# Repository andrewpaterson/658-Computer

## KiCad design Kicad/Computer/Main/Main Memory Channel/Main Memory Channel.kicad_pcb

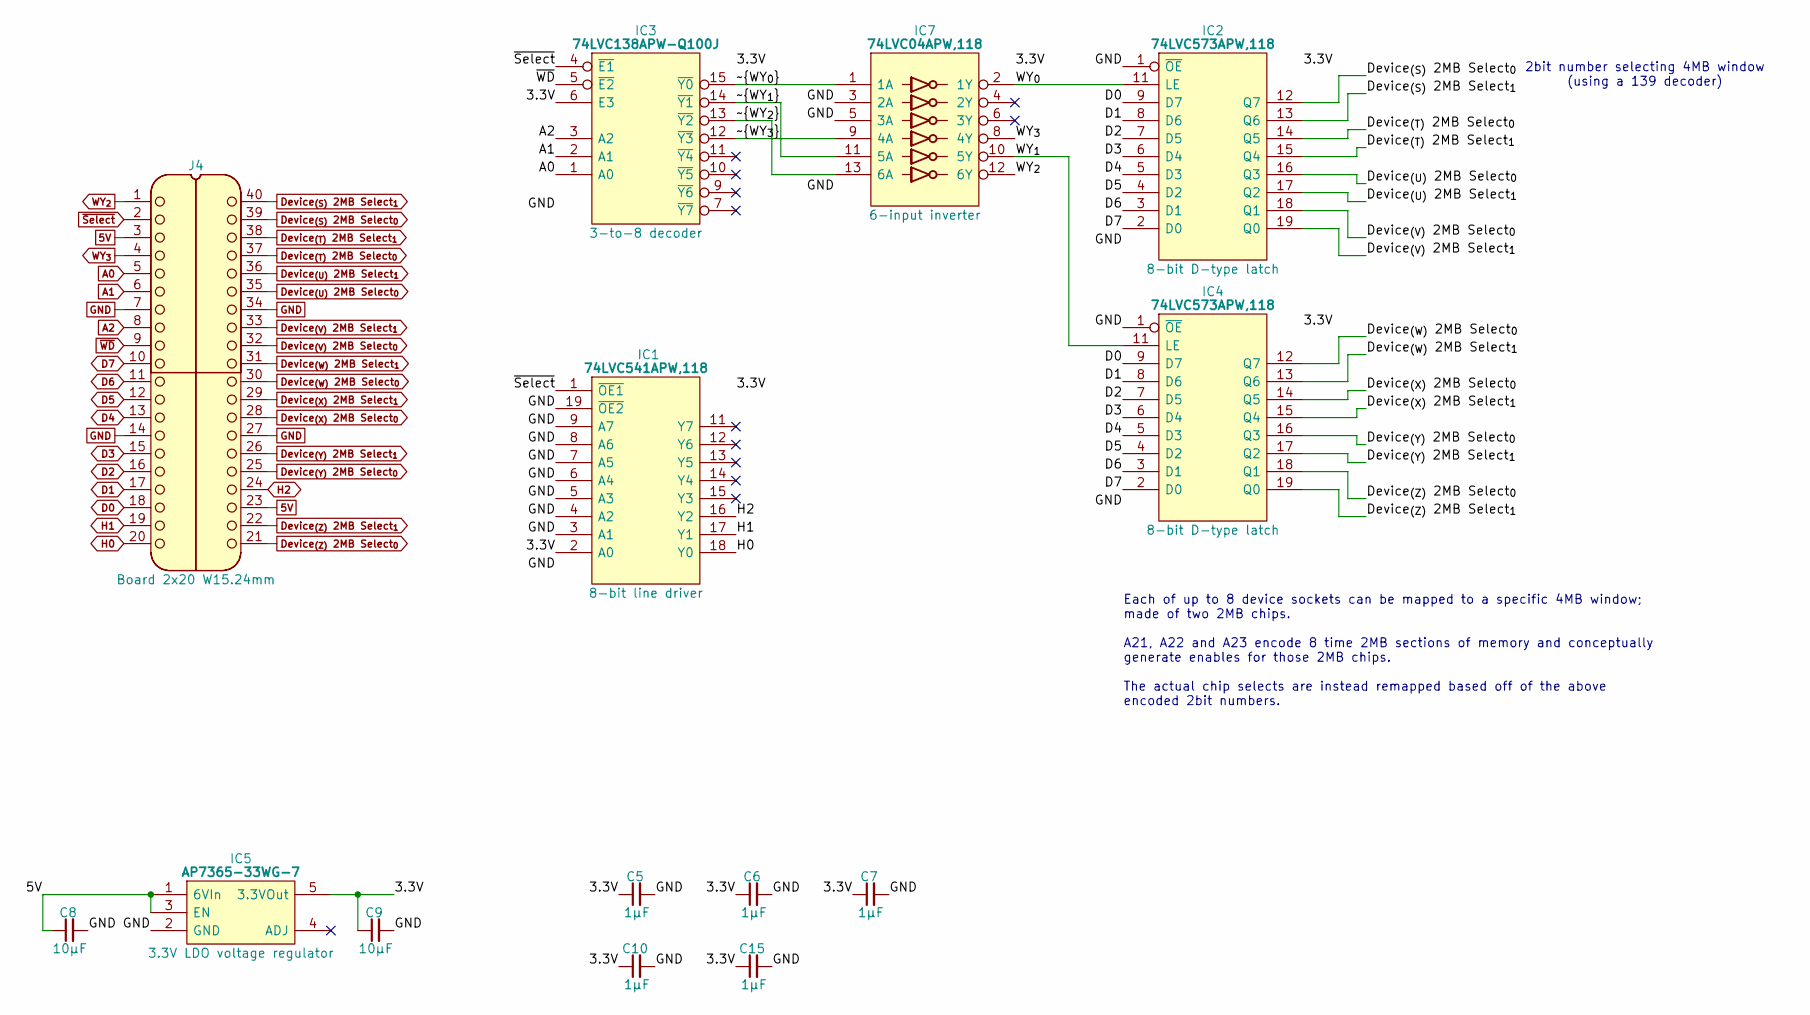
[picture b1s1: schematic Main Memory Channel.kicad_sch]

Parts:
C5, C6, C7, C10, C15: 1μF; C_0805
C8, C9: 10µF; C_0805
IC1: 74LVC541APW,118; SOP65P640X110-20N; Mouser Part Number 771-74LVC541APW-T
IC2, IC4: 74LVC573APW,118; SOP65P640X110-20N; Mouser Part Number 771-74LVC573APW-T
IC3: 74LVC138APW-Q100J; SOP65P640X110-16N; Mouser Part Number 771-74LVC138APWQ100J
IC5: AP7365-33WG-7; SOT95P285X130-5N; Manufacturer_Part_Number AP7365-33WG-7; Mouser Part Number 621-AP7365-33WG-7
IC7: 74LVC04APW,118; SOP65P640X110-14N; Manufacturer_Part_Number 74LVC04APW,118; Mouser Part Number 771-74LVC04APW-T
J4: Board 2x20 W15.24mm; DIP-40_Board_W15.24mm

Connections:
5V: C8.1, IC5.1 (6VIn), IC5.3 (EN), J4.3, J4.23
/3.3V: C5.1, C6.1, C7.1, C9.1, C10.1, C15.1, IC1.2 (A0), IC1.20 (3V), IC2.20 (3V), IC3.6 (E3), IC3.16 (3V), IC4.20 (3V), IC5.5 (3.3VOut), IC7.14 (3V)
/WY_{0}: IC2.11 (LE), IC7.2 (1Y)
/WY_{1}: IC4.11 (LE), IC7.10 (5Y)
/~WY_{0}: IC3.15 (~Y0), IC7.1 (1A)
/~WY_{1}: IC3.14 (~Y1), IC7.11 (5A)
/~WY_{2}: IC3.13 (~Y2), IC7.13 (6A)
/~WY_{3}: IC3.12 (~Y3), IC7.9 (4A)
A0: IC3.1 (A0), J4.5
A1: IC3.2 (A1), J4.6
A2: IC3.3 (A2), J4.8
D0: IC2.9 (D7), IC4.9 (D7), J4.18
D1: IC2.8 (D6), IC4.8 (D6), J4.17
D2: IC2.7 (D5), IC4.7 (D5), J4.16
D3: IC2.6 (D4), IC4.6 (D4), J4.15
D4: IC2.5 (D3), IC4.5 (D3), J4.13
D5: IC2.4 (D2), IC4.4 (D2), J4.12
D6: IC2.3 (D1), IC4.3 (D1), J4.11
D7: IC2.2 (D0), IC4.2 (D0), J4.10
Device_{(S)} 2MB Select_{0}: IC2.12 (Q7), J4.39
Device_{(S)} 2MB Select_{1}: IC2.13 (Q6), J4.40
Device_{(T)} 2MB Select_{0}: IC2.14 (Q5), J4.37
Device_{(T)} 2MB Select_{1}: IC2.15 (Q4), J4.38
Device_{(U)} 2MB Select_{0}: IC2.16 (Q3), J4.35
Device_{(U)} 2MB Select_{1}: IC2.17 (Q2), J4.36
Device_{(V)} 2MB Select_{0}: IC2.18 (Q1), J4.32
Device_{(V)} 2MB Select_{1}: IC2.19 (Q0), J4.33
Device_{(W)} 2MB Select_{0}: IC4.12 (Q7), J4.30
Device_{(W)} 2MB Select_{1}: IC4.13 (Q6), J4.31
Device_{(X)} 2MB Select_{0}: IC4.14 (Q5), J4.28
Device_{(X)} 2MB Select_{1}: IC4.15 (Q4), J4.29
Device_{(Y)} 2MB Select_{0}: IC4.16 (Q3), J4.25
Device_{(Y)} 2MB Select_{1}: IC4.17 (Q2), J4.26
Device_{(Z)} 2MB Select_{0}: IC4.18 (Q1), J4.21
Device_{(Z)} 2MB Select_{1}: IC4.19 (Q0), J4.22
GND: C5.2, C6.2, C7.2, C8.2, C9.2, C10.2, C15.2, IC1.3 (A1), IC1.4 (A2), IC1.5 (A3), IC1.6 (A4), IC1.7 (A5), IC1.8 (A6), IC1.9 (A7), IC1.10 (GND), IC1.19 (~OE2), IC2.1 (~OE), IC2.10 (GND), IC3.8 (GND), IC4.1 (~OE), IC4.10 (GND), IC5.2 (GND), IC7.3 (2A), IC7.5 (3A), IC7.7 (GND), J4.7, J4.14, J4.27, J4.34
H0: IC1.18 (Y0), J4.20
H1: IC1.17 (Y1), J4.19
H2: IC1.16 (Y2), J4.24
WY_{2}: IC7.12 (6Y), J4.1
WY_{3}: IC7.8 (4Y), J4.4
~Select: IC1.1 (~OE1), IC3.4 (~E1), J4.2
~WD: IC3.5 (~E2), J4.9

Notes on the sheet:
Each of up to 8 device sockets can be mapped to a specific 4MB window; made of two 2MB chips. A21, A22 and A23 encode 8 time 2MB sections of memory and conceptually generate enables for those 2MB chips. The actual chip selects are instead remapped based off of the above encoded 2bit numbers.
2bit number selecting 4MB window (using a 139 decoder)

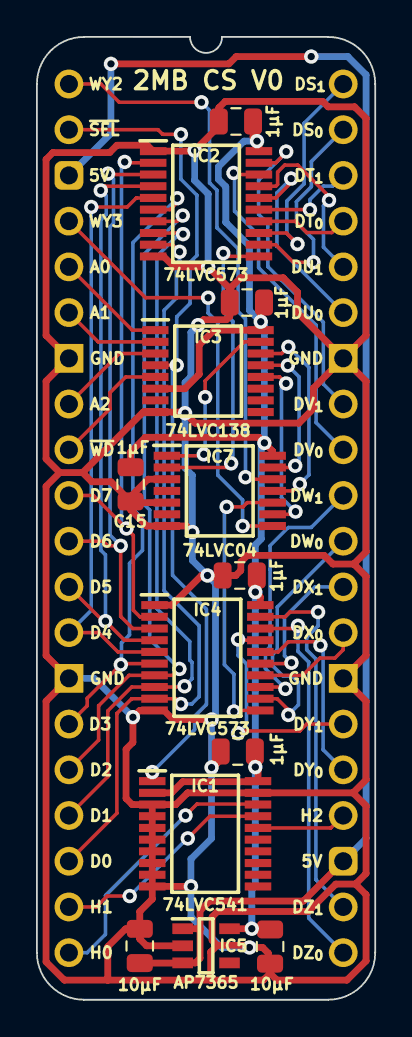
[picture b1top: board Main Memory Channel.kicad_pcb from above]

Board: 2 copper layers, 18.8 x 53.5 mm, 14 parts (0 on the bottom side), 43 nets.

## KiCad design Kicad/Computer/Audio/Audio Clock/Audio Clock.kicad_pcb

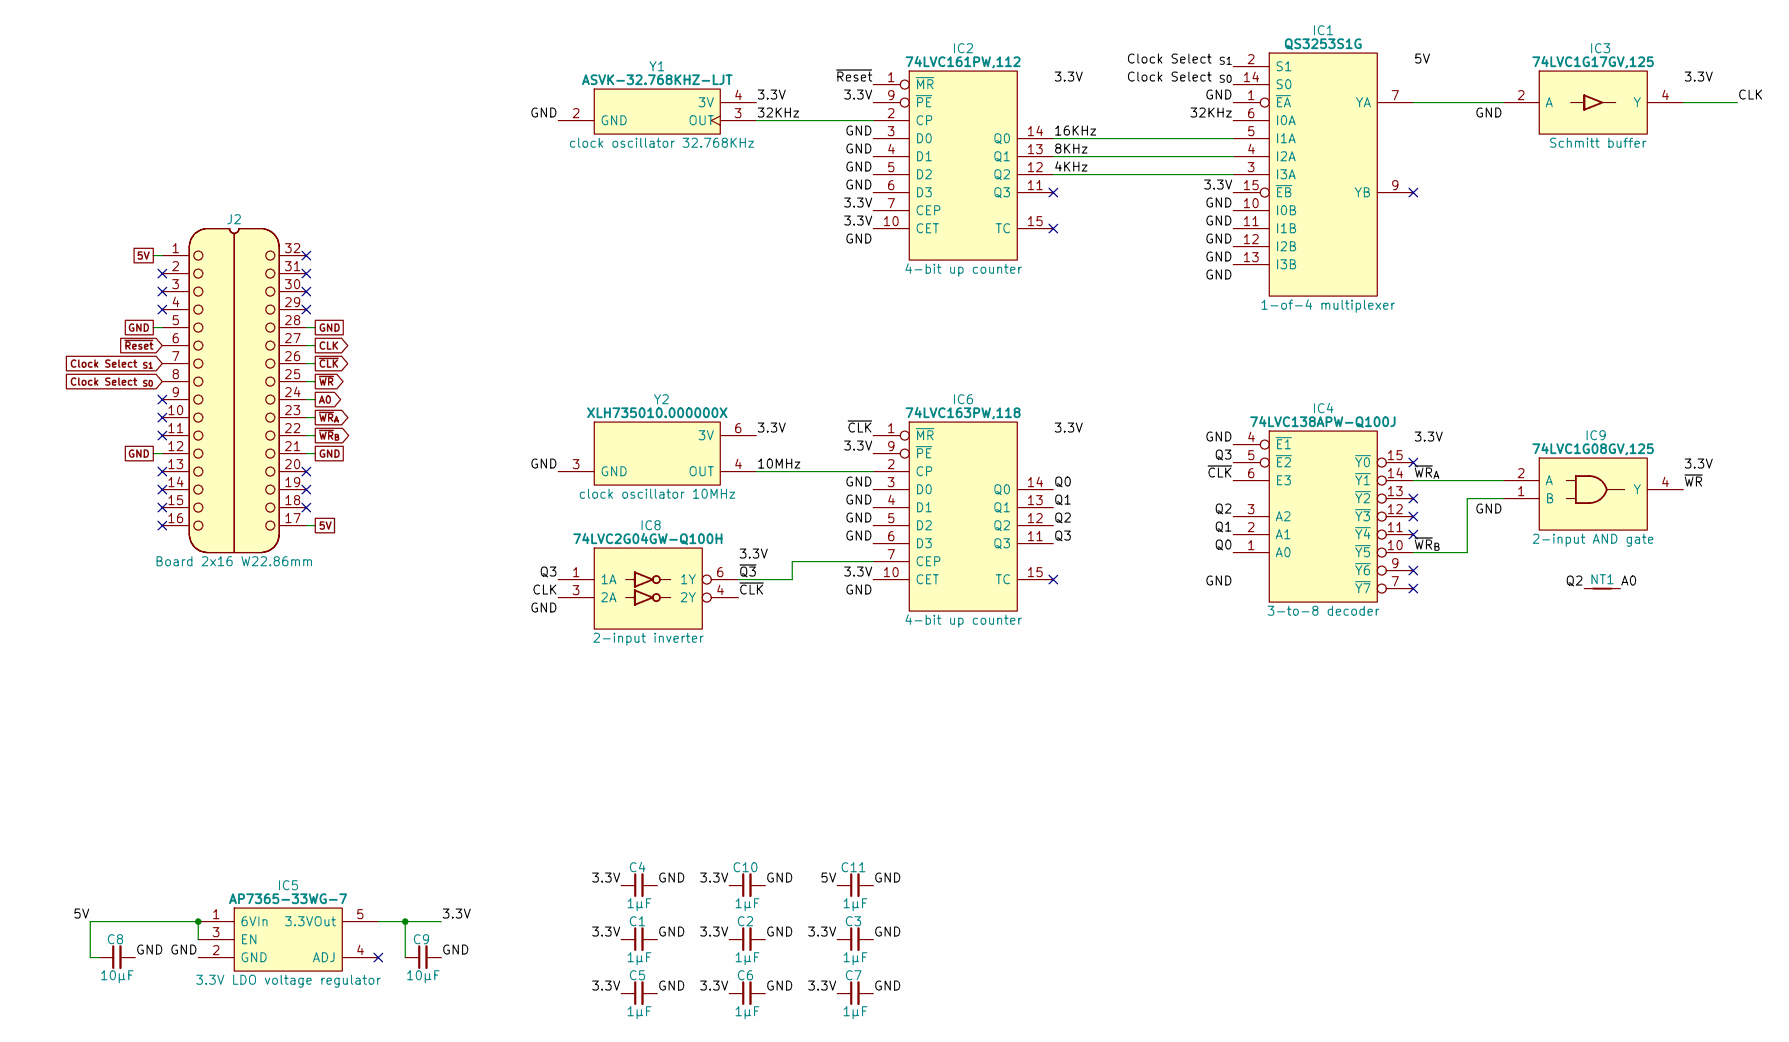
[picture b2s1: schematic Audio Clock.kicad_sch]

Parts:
C1, C2, C3, C4, C5, C6, C7, C10, C11: 1μF; C_0805
C8, C9: 10µF; C_0805
IC1: QS3253S1G; SOIC127P602X173-16N; Manufacturer_Part_Number QS3253S1G
IC2: 74LVC161PW,112; SOP65P640X110-16N; Mouser Part Number 771-LVC161PW112
IC3: 74LVC1G17GV,125; SOT95P275X110-5N; Manufacturer_Part_Number 74LVC1G17GV,125
IC4: 74LVC138APW-Q100J; SOP65P640X110-16N; Mouser Part Number 771-74LVC138APWQ100J
IC5: AP7365-33WG-7; SOT95P285X130-5N; Manufacturer_Part_Number AP7365-33WG-7; Mouser Part Number 621-AP7365-33WG-7
IC6: 74LVC163PW,118; SOP65P640X110-16N; Mouser Part Number 771-74LVC163PW-T
IC8: 74LVC2G04GW-Q100H; SOP65P210X110-6N; Manufacturer_Part_Number 74LVC2G04GW-Q100H; Mouser Part Number 771-74LVC2G04GWQ100H
IC9: 74LVC1G08GV,125; SOT95P275X110-5N; Manufacturer_Part_Number 74LVC1G08GV,125; Mouser Part Number 771-74LVC1G08GV
J2: Board 2x16 W22.86mm; DIP-32_Board_W22.86mm
NT1: NetTie; NetTie-2_SMD_Pad0.5mm
Y1: ASVK-32.768KHZ-LJT; ASVK32768KHZLJT; Manufacturer_Part_Number ASVK-32.768KHZ-LJT; Mouser Part Number 815-ASVK-32.768KLJT
Y2: XLH735010.000000X; XLH735100000000I; Manufacturer_Part_Number XLH735010.000000X; Mouser Part Number 972-XLH735010000000X

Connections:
5V: C8.1, C11.1, IC1.16 (5V), IC5.1 (6VIn), IC5.3 (EN), J2.1, J2.17
/3.3V: C1.1, C2.1, C3.1, C4.1, C5.1, C6.1, C7.1, C9.1, C10.1, IC1.15 (~EB), IC2.7 (CEP), IC2.9 (~PE), IC2.10 (CET), IC2.16 (3V), IC3.5 (3V), IC4.16 (3V), IC5.5 (3.3VOut), IC6.9 (~PE), IC6.10 (CET), IC6.16 (3V), IC8.5 (3V), IC9.5 (3V), Y1.4 (3V), Y2.6 (3V)
/4KHz: IC1.3 (I3A), IC2.12 (Q2)
/8KHz: IC1.4 (I2A), IC2.13 (Q1)
/10MHz: IC6.2 (CP), Y2.4 (OUT)
/16KHz: IC1.5 (I1A), IC2.14 (Q0)
/32KHz: IC1.6 (I0A), IC2.2 (CP), Y1.3 (OUT)
/Q0: IC4.1 (A0), IC6.14 (Q0)
/Q1: IC4.2 (A1), IC6.13 (Q1)
/Q2: IC4.3 (A2), IC6.12 (Q2), NT1.1
/Q3: IC4.5 (~E2), IC6.11 (Q3), IC8.1 (1A)
/~Q3: IC6.7 (CEP), IC8.6 (1Y)
A0: J2.24, NT1.2
CLK: IC3.4 (Y), IC8.3 (2A), J2.27
Clock Select _{S0}: IC1.14 (S0), J2.8
Clock Select _{S1}: IC1.2 (S1), J2.7
GND: C1.2, C2.2, C3.2, C4.2, C5.2, C6.2, C7.2, C8.2, C9.2, C10.2, C11.2, IC1.1 (~EA), IC1.8 (GND), IC1.10 (I0B), IC1.11 (I1B), IC1.12 (I2B), IC1.13 (I3B), IC2.3 (D0), IC2.4 (D1), IC2.5 (D2), IC2.6 (D3), IC2.8 (GND), IC3.3 (GND), IC4.4 (~E1), IC4.8 (GND), IC5.2 (GND), IC6.3 (D0), IC6.4 (D1), IC6.5 (D2), IC6.6 (D3), IC6.8 (GND), IC8.2 (GND), IC9.3 (GND), J2.5, J2.12, J2.21, J2.28, Y1.2 (GND), Y2.3 (GND)
unnamed: IC1.7 (YA), IC3.2 (A)
~CLK: IC4.6 (E3), IC6.1 (~MR), IC8.4 (2Y), J2.26
~Reset: IC2.1 (~MR), J2.6
~WR: IC9.4 (Y), J2.25
~WR_{A}: IC4.14 (~Y1), IC9.2 (A), J2.23
~WR_{B}: IC4.10 (~Y5), IC9.1 (B), J2.22

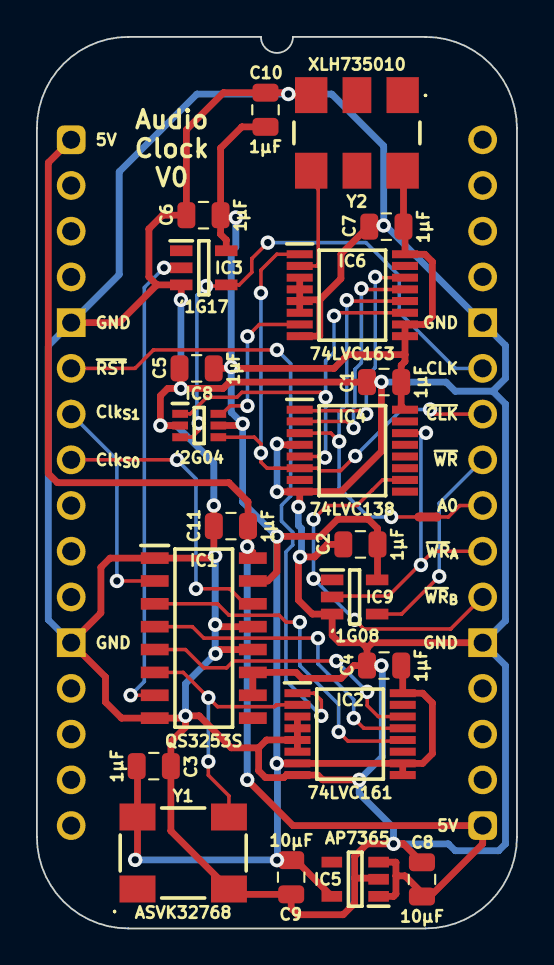
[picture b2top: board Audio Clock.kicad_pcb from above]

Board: 2 copper layers, 26.7 x 49.5 mm, 23 parts (0 on the bottom side), 23 nets.

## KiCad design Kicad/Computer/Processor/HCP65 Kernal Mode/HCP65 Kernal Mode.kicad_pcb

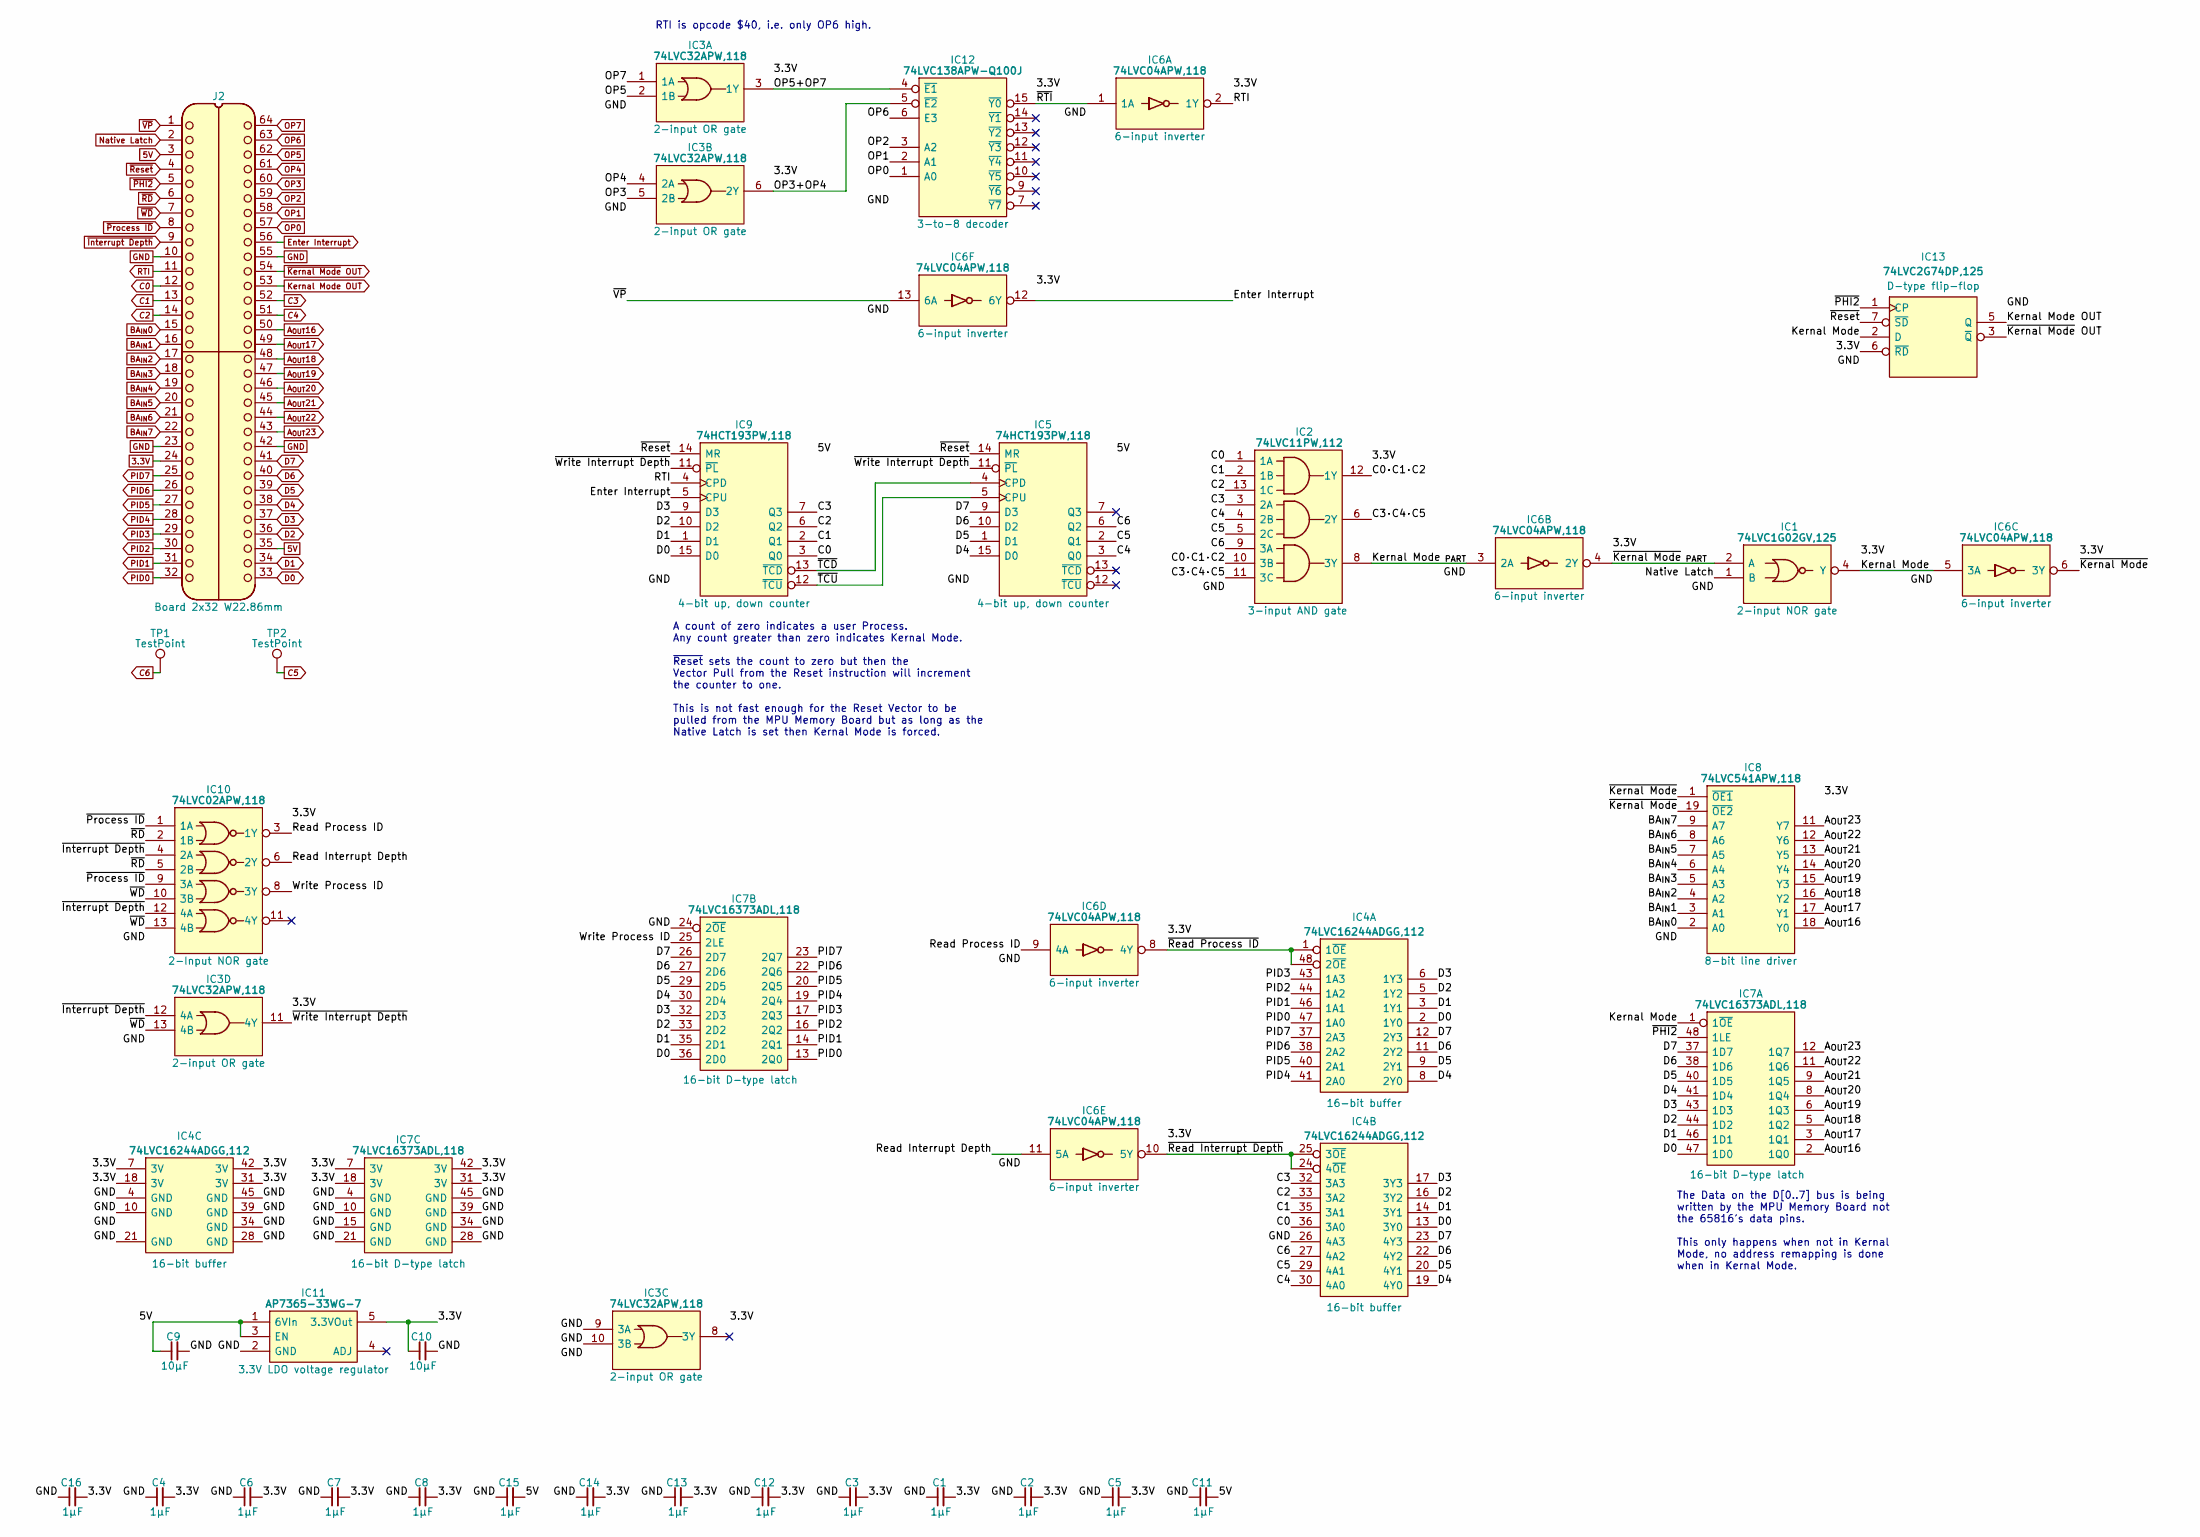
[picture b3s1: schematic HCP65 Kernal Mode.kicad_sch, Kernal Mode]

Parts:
C1, C2, C3, C4, C5, C6, C7, C8, C11, C12, C13, C14, C15, C16: 1μF; C_0805
C9, C10: 10μF; C_0805
IC1: 74LVC1G02GV,125; SOT95P275X110-5N; Manufacturer_Part_Number 74LVC1G02GV,125; Mouser Part Number 771-LVC1G02GV125
IC2: 74LVC11PW,112; SOP65P640X110-14N; Mouser Part Number 771-LVC11PW112
IC3: 74LVC32APW,118; SOP65P640X110-14N; Manufacturer_Part_Number 74LVC32APW,118; Mouser Part Number 771-74LVC32APW-T
IC4: 74LVC16244ADGG,112; 74LVC16244ADGG112; Manufacturer_Part_Number 74LVC16244ADGG,112; Mouser Part Number 771-74LVC16244DG
IC5, IC9: 74HCT193PW,118; SOP65P640X110-16N; Manufacturer_Part_Number 74HCT193PW,118; Mouser Part Number 771-HCT193PW118
IC6: 74LVC04APW,118; SOP65P640X110-14N; Manufacturer_Part_Number 74LVC04APW,118; Mouser Part Number 771-74LVC04APW-T
IC7: 74LVC16373ADL,118; SOP64P1025X280-48N; Mouser Part Number 771-LVC16373ADL118
IC8: 74LVC541APW,118; SOP65P640X110-20N; Mouser Part Number 771-74LVC541APW-T
IC10: 74LVC02APW,118; SOP65P640X110-14N; Mouser Part Number 771-74LVC02APW-T
IC11: AP7365-33WG-7; SOT95P285X130-5N; Manufacturer_Part_Number AP7365-33WG-7; Mouser Part Number 621-AP7365-33WG-7
IC12: 74LVC138APW-Q100J; SOP65P640X110-16N; Mouser Part Number 771-74LVC138APWQ100J
IC13: 74LVC2G74DP,125; SOP65P400X110-8N; Manufacturer_Part_Number 74LVC2G74DP,125; Mouser Part Number 771-74LVC2G74DP-G
J2: Board 2x32 W22.86mm; DIP-64_Board_W22.86mm
TP1, TP2: TestPoint; PinHeader_1x01_P2.54mm_Vertical

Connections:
3.3V: C1.2, C2.2, C3.2, C4.2, C5.2, C6.2, C7.2, C8.2, C10.1, C12.2, C13.2, C14.2, C16.2, IC1.5 (3V), IC2.14 (3V), IC3.14 (3V), IC4.7 (3V), IC4.18 (3V), IC4.31 (3V), IC4.42 (3V), IC6.14 (3V), IC7.7 (3V), IC7.18 (3V), IC7.31 (3V), IC7.42 (3V), IC8.20 (3V), IC10.14 (3V), IC11.5 (3.3VOut), IC12.16 (3V), IC13.6 (~RD), J2.24
5V: C9.1, C11.2, C15.2, IC5.16 (5V), IC9.16 (5V), IC11.1 (6VIn), IC11.3 (EN), J2.3, J2.35
/C0·C1·C2: IC2.10 (3B), IC2.12 (1Y)
/C3·C4·C5: IC2.6 (2Y), IC2.11 (3C)
/Kernal Mode: IC1.4 (Y), IC6.5 (3A), IC7.1 (1~OE), IC13.2 (D)
/Kernal Mode_{ PART}: IC2.8 (3Y), IC6.3 (2A)
/OP3+OP4: IC3.6 (2Y), IC12.5 (~E2)
/OP5+OP7: IC3.3 (1Y), IC12.4 (~E1)
/Read Interrupt Depth: IC6.11 (5A), IC10.6 (2Y)
/Read Process ID: IC6.9 (4A), IC10.3 (1Y)
/Write Process ID: IC7.25 (2LE), IC10.8 (3Y)
/~Kernal Mode: IC6.6 (3Y), IC8.1 (~OE1), IC8.19 (~OE2)
/~Kernal Mode_{ PART}: IC1.2 (A), IC6.4 (2Y)
/~RTI: IC6.1 (1A), IC12.15 (~Y0)
/~Read Interrupt Depth: IC4.24 (4~OE), IC4.25 (3~OE), IC6.10 (5Y)
/~Read Process ID: IC4.1 (1~OE), IC4.48 (2~OE), IC6.8 (4Y)
/~TCD: IC5.4 (CPD), IC9.13 (~TCD)
/~TCU: IC5.5 (CPU), IC9.12 (~TCU)
/~Write Interrupt Depth: IC3.11 (4Y), IC5.11 (~PL), IC9.11 (~PL)
A_{OUT}16: IC7.2 (1Q0), IC8.18 (Y0), J2.50
A_{OUT}17: IC7.3 (1Q1), IC8.17 (Y1), J2.49
A_{OUT}18: IC7.5 (1Q2), IC8.16 (Y2), J2.48
A_{OUT}19: IC7.6 (1Q3), IC8.15 (Y3), J2.47
A_{OUT}20: IC7.8 (1Q4), IC8.14 (Y4), J2.46
A_{OUT}21: IC7.9 (1Q5), IC8.13 (Y5), J2.45
A_{OUT}22: IC7.11 (1Q6), IC8.12 (Y6), J2.44
A_{OUT}23: IC7.12 (1Q7), IC8.11 (Y7), J2.43
BA_{IN}0: IC8.2 (A0), J2.15
BA_{IN}1: IC8.3 (A1), J2.16
BA_{IN}2: IC8.4 (A2), J2.17
BA_{IN}3: IC8.5 (A3), J2.18
BA_{IN}4: IC8.6 (A4), J2.19
BA_{IN}5: IC8.7 (A5), J2.20
BA_{IN}6: IC8.8 (A6), J2.21
BA_{IN}7: IC8.9 (A7), J2.22
C0: IC2.1 (1A), IC4.36 (3A0), IC9.3 (Q0), J2.12
C1: IC2.2 (1B), IC4.35 (3A1), IC9.2 (Q1), J2.13
C2: IC2.13 (1C), IC4.33 (3A2), IC9.6 (Q2), J2.14
C3: IC2.3 (2A), IC4.32 (3A3), IC9.7 (Q3), J2.52
C4: IC2.4 (2B), IC4.30 (4A0), IC5.3 (Q0), J2.51
C5: IC2.5 (2C), IC4.29 (4A1), IC5.2 (Q1), TP2.1 (1_1)
C6: IC2.9 (3A), IC4.27 (4A2), IC5.6 (Q2), TP1.1 (1_1)
D0: IC4.2 (1Y0), IC4.13 (3Y0), IC7.36 (2D0), IC7.47 (1D0), IC9.15 (D0), J2.33
D1: IC4.3 (1Y1), IC4.14 (3Y1), IC7.35 (2D1), IC7.46 (1D1), IC9.1 (D1), J2.34
D2: IC4.5 (1Y2), IC4.16 (3Y2), IC7.33 (2D2), IC7.44 (1D2), IC9.10 (D2), J2.36
D3: IC4.6 (1Y3), IC4.17 (3Y3), IC7.32 (2D3), IC7.43 (1D3), IC9.9 (D3), J2.37
D4: IC4.8 (2Y0), IC4.19 (4Y0), IC5.15 (D0), IC7.30 (2D4), IC7.41 (1D4), J2.38
D5: IC4.9 (2Y1), IC4.20 (4Y1), IC5.1 (D1), IC7.29 (2D5), IC7.40 (1D5), J2.39
D6: IC4.11 (2Y2), IC4.22 (4Y2), IC5.10 (D2), IC7.27 (2D6), IC7.38 (1D6), J2.40
D7: IC4.12 (2Y3), IC4.23 (4Y3), IC5.9 (D3), IC7.26 (2D7), IC7.37 (1D7), J2.41
Enter Interrupt: IC6.12 (6Y), IC9.5 (CPU), J2.56
GND: C1.1, C2.1, C3.1, C4.1, C5.1, C6.1, C7.1, C8.1, C9.2, C10.2, C11.1, C12.1, C13.1, C14.1, C15.1, C16.1, IC1.3 (GND), IC2.7 (GND), IC3.7 (GND), IC3.9 (3A), IC3.10 (3B), IC4.4 (GND), IC4.10 (GND), IC4.15 (GND), IC4.21 (GND), IC4.26 (4A3), IC4.28 (GND), IC4.34 (GND), IC4.39 (GND), IC4.45 (GND), IC5.8 (GND), IC6.7 (GND), IC7.4 (GND), IC7.10 (GND), IC7.15 (GND), IC7.21 (GND), IC7.24 (2~OE), IC7.28 (GND), IC7.34 (GND), IC7.39 (GND), IC7.45 (GND), IC8.10 (GND), IC9.8 (GND), IC10.7 (GND), IC11.2 (GND), IC12.8 (GND), IC13.4 (GND), IC13.8 (3V), J2.10, J2.23, J2.42, J2.55
Kernal Mode OUT: IC13.5 (Q), J2.53
Native Latch: IC1.1 (B), J2.2
OP0: IC12.1 (A0), J2.57
OP1: IC12.2 (A1), J2.58
OP2: IC12.3 (A2), J2.59
OP3: IC3.5 (2B), J2.60
OP4: IC3.4 (2A), J2.61
OP5: IC3.2 (1B), J2.62
OP6: IC12.6 (E3), J2.63
OP7: IC3.1 (1A), J2.64
PID0: IC4.47 (1A0), IC7.13 (2Q0), J2.32
PID1: IC4.46 (1A1), IC7.14 (2Q1), J2.31
PID2: IC4.44 (1A2), IC7.16 (2Q2), J2.30
PID3: IC4.43 (1A3), IC7.17 (2Q3), J2.29
PID4: IC4.41 (2A0), IC7.19 (2Q4), J2.28
PID5: IC4.40 (2A1), IC7.20 (2Q5), J2.27
PID6: IC4.38 (2A2), IC7.22 (2Q6), J2.26
PID7: IC4.37 (2A3), IC7.23 (2Q7), J2.25
RTI: IC6.2 (1Y), IC9.4 (CPD), J2.11
~Interrupt Depth: IC3.12 (4A), IC10.4 (2A), IC10.12 (4A), J2.9
~Kernal Mode OUT: IC13.3 (~Q), J2.54
~PHI2: IC7.48 (1LE), IC13.1 (CP), J2.5
~Process ID: IC10.1 (1A), IC10.9 (3A), J2.8
~RD: IC10.2 (1B), IC10.5 (2B), J2.6
~Reset: IC5.14 (MR), IC9.14 (MR), IC13.7 (~SD), J2.4
~VP: IC6.13 (6A), J2.1
~WD: IC3.13 (4B), IC10.10 (3B), IC10.13 (4B), J2.7

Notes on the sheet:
RTI is opcode $40, i.e. only OP6 high.
The Data on the D[0..7] bus is being written by the MPU Memory Board not the 65816's data pins. This only happens when not in Kernal Mode, no address remapping is done when in Kernal Mode.
A count of zero indicates a user Process. Any count greater than zero indicates Kernal Mode. ~{Reset} sets the count to zero but then the Vector Pull from the Reset instruction will increment the counter to one. This is not fast enough for the Reset Vector to be pulled from the MPU Memory Board but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

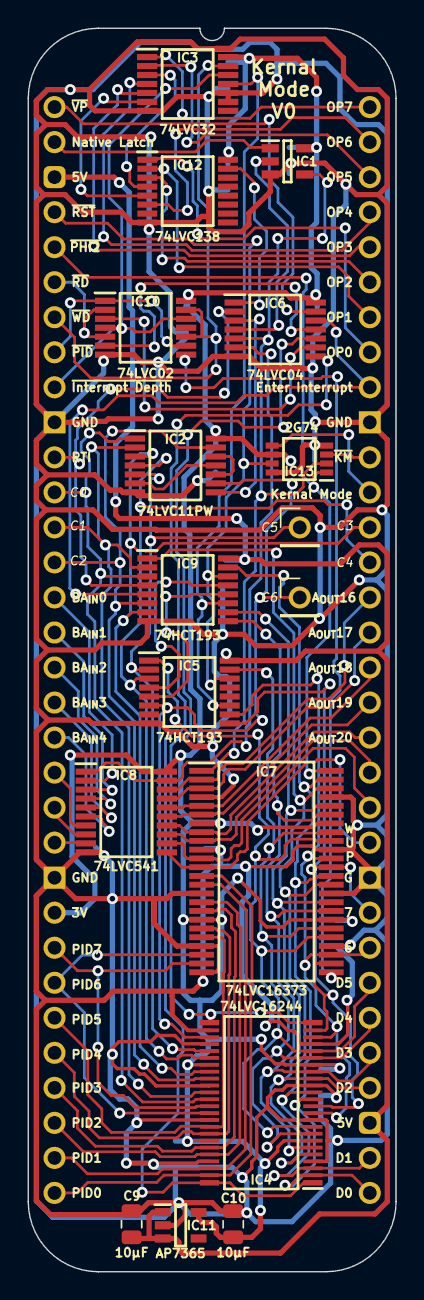
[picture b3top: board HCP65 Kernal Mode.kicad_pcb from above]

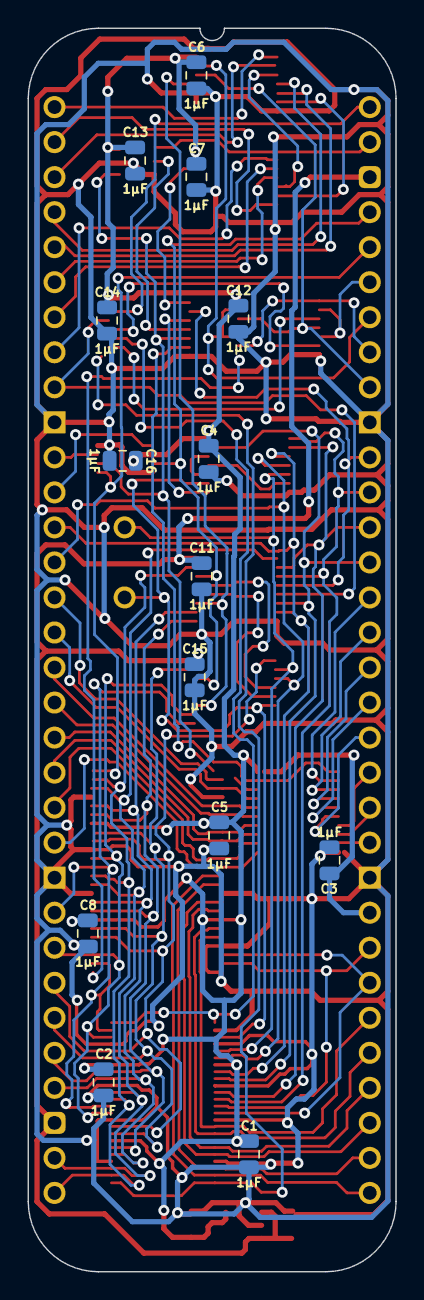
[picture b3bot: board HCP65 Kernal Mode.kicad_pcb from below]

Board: 2 copper layers, 26.7 x 90.2 mm, 32 parts (14 on the bottom side), 79 nets.

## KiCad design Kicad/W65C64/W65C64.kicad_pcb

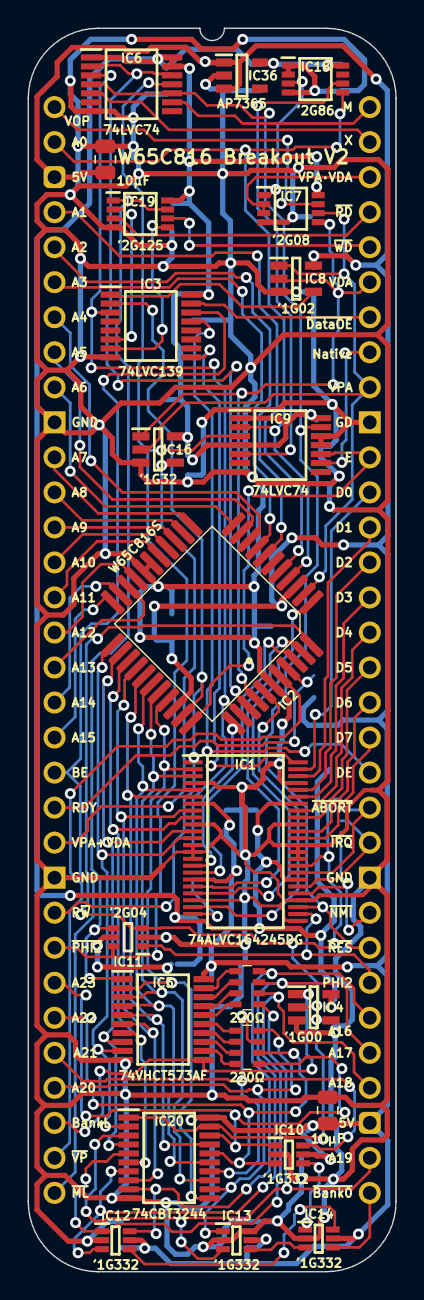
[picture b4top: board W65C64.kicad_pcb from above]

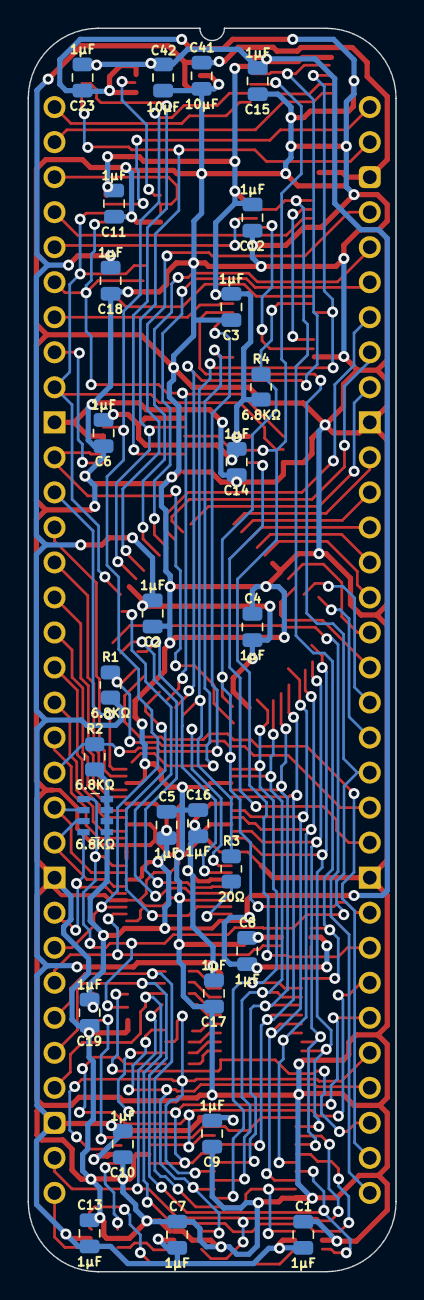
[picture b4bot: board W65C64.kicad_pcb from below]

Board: 2 copper layers, 26.7 x 90.2 mm, 51 parts (27 on the bottom side), 96 nets.

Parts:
C1, C2, C3, C4, C5, C6, C7, C8, C9, C10, C11, C12, C13, C14, C15, C16, C17, C18, C19, C23: 1μF; C_0805
C20, C21, C41, C42: 10μF; C_0805
IC1: 74ALVC164245DGG,11; SOP50P810X120-48N
IC2: W65C816S6TQG-14; W65C816 PLCC 0.8mm 44 Pin
IC3: 74LVC139PW,118; SOP65P640X110-16N
IC4: 74LVC1G00GV,125; SOT95P275X110-5N
IC5: 74VHCT573AFT; SOP65P640X120-20N
IC6, IC9: 74LVC74APW,118; SOP65P640X110-14N
IC7: 74LVC2G08DP-Q100H; SOP65P400X110-8N
IC8: 74LVC1G02GV,125; SOT95P275X110-5N
IC10, IC12, IC13, IC14: SN74LVC1G332DCKRG4; SOT65P210X110-6N
IC11: 74LVC2G04GW-Q100H; SOP65P210X110-6N
IC16: 74LVC1G32GV,125; SOT95P275X110-5N
IC18: 74LVC2G86DP,125; SOP65P400X110-8N
IC19: 74LVC2G125DP,125; SOP65P400X110-8N
IC20: SN74CBT3244CPWR; SOP65P640X120-20N
IC36: AP7365-33WG-7; SOT95P285X130-5N
J7: Board 2x32 W22.86mm; DIP-64_Board_W22.86mm
R1, R2, R4: 6.8KΩ; R_0805
R3: 20Ω; R_0805
RN1, RN2: CAY16-221J4LF; CAY16-F4
RN4: CAY16-472J4LF; CAY16-F4

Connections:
5V: C1.1, C2.1, C4.1, C7.1, C9.1, C10.1, C13.1, C16.1, C17.1, C18.1, C20.1, C21.1, C41.1, IC1.7 (5V), IC1.18 (5V), IC2.9 (VCC), IC2.37 (VCC), IC5.20 (5V), IC8.5 (3V), IC10.5 (3V), IC12.5 (3V), IC13.5 (3V), IC14.5 (3V), IC20.20 (5V), IC36.1 (6VIn), IC36.3 (EN), J7.3, J7.35, R1.1
/3.3V: C3.1, C5.1, C6.1, C8.1, C11.1, C12.1, C14.1, C15.1, C19.1, C23.1, C42.1, IC1.24 (2DIR), IC1.31 (3V), IC1.42 (3V), IC3.16 (3V), IC4.5 (3V), IC6.1 (~1RD), IC6.13 (~2RD), IC6.14 (3V), IC7.8 (3V), IC9.1 (~1RD), IC9.4 (~1SD), IC9.14 (3V), IC11.5 (3V), IC16.5 (3V), IC18.8 (VCC), IC19.8 (VCC), IC36.5 (3.3VOut), R2.1, R4.1, RN4.1 (R1), RN4.2 (R2), RN4.3 (R3), RN4.4 (R4)
/A0_{CHANGE}: IC7.1 (1A), IC18.3 (2Y)
/A0_{PREV}: IC9.5 (1Q), IC18.6 (2B)
/BA0+BA1+BA2: IC12.4 (Y), IC14.6 (C)
/BA3+BA4: IC13.4 (Y), IC14.3 (B)
/BA5+BA6+BA7: IC10.4 (Y), IC14.1 (A)
/BE_{5V}: IC1.16 (2B2), IC2.40 (BE)
/D0_{65}: IC1.2 (1B0), IC2.36 (D0), IC5.2 (D0), IC20.11 (2A1)
/D0_{VHC}: IC5.19 (Q0), RN2.1 (R1)
/D1_{65}: IC1.3 (1B1), IC2.35 (D1), IC5.3 (D1), IC20.13 (2A2)
/D1_{VHC}: IC5.18 (Q1), RN2.2 (R2)
/D2_{65}: IC1.5 (1B2), IC2.34 (D2), IC5.4 (D2), IC20.15 (2A3)
/D2_{VHC}: IC5.17 (Q2), RN2.3 (R3)
/D3_{65}: IC1.6 (1B3), IC2.33 (D3), IC5.5 (D3), IC20.17 (2A4)
/D3_{VHC}: IC5.16 (Q3), RN2.4 (R4)
/D4_{65}: IC1.8 (1B4), IC2.32 (D4), IC5.6 (D4), IC20.8 (1A4)
/D4_{VHC}: IC5.15 (Q4), RN1.1 (R1)
/D5_{65}: IC1.9 (1B5), IC2.31 (D5), IC5.7 (D5), IC20.6 (1A3)
/D5_{VHC}: IC5.14 (Q5), RN1.2 (R2)
/D6_{65}: IC1.11 (1B6), IC2.30 (D6), IC5.8 (D6), IC20.4 (1A2)
/D6_{VHC}: IC5.13 (Q6), RN1.3 (R3)
/D7_{65}: IC1.12 (1B7), IC2.29 (D7), IC5.9 (D7), IC20.2 (1A1)
/D7_{VHC}: IC5.12 (Q7), RN1.4 (R4)
/FET ~OE: IC4.4 (Y), IC20.1 (1~OE), IC20.19 (2~OE)
/MX: IC2.42 (MX), IC6.2 (1D), IC6.12 (2D)
/PHI2_{5V}: IC2.41 (PHI2), IC3.3 (1A1), IC6.3 (1CP), R3.2
/~ABORT_{5V}: IC1.17 (2B3), IC2.4 (~ABORT)
/~BE: IC5.1 (~OE), IC11.4 (2Y), IC19.1 (1~OE), IC19.7 (2~OE)
/~DE: IC1.48 (1~OE), IC3.9 (~2Y3)
/~IRQ_{5V}: IC1.19 (2B4), IC2.5 (~IRQ)
/~NMI_{5V}: IC1.20 (2B5), IC2.7 (~NMI)
/~RD_{PART}: IC3.7 (~1Y3), IC19.5 (2A)
/~RES_{5V}: IC1.22 (2B6), IC2.44 (~RES)
/~VPA+VDA: IC3.1 (~1E), IC8.4 (Y)
/~WD_{PART}: IC3.6 (~1Y2), IC19.2 (1A)
A0: IC2.10 (A0), IC9.2 (1D), IC18.5 (2A), J7.2
A1: IC2.11 (A1), J7.4
A2: IC2.13 (A2), J7.5
A3: IC2.14 (A3), J7.6
A4: IC2.15 (A4), J7.7
A5: IC2.16 (A5), J7.8
A6: IC2.17 (A6), J7.9
A7: IC2.18 (A7), J7.11
A8: IC2.19 (A8), J7.12
A9: IC2.20 (A9), J7.13
A10: IC2.21 (A10), J7.14
A11: IC2.22 (A11), J7.15
A12: IC2.25 (A12), J7.16
A13: IC2.26 (A13), J7.17
A14: IC2.27 (A14), J7.18
A15: IC2.28 (A15), J7.19
Address Valid: IC16.4 (Y), J7.22
BA0: IC12.6 (C), IC20.9 (2B1), J7.38, RN2.8 (R1)
BA1: IC12.3 (B), IC20.7 (2B2), J7.37, RN2.7 (R2)
BA2: IC12.1 (A), IC20.5 (2B3), J7.36, RN2.6 (R3)
BA3: IC13.3 (B), IC20.3 (2B4), J7.34, RN2.5 (R4)
BA4: IC13.1 (A), IC20.12 (1B4), J7.29, RN1.8 (R1)
BA5: IC10.6 (C), IC20.14 (1B3), J7.28, RN1.7 (R2)
BA6: IC10.3 (B), IC20.16 (1B2), J7.27, RN1.6 (R3)
BA7: IC10.1 (A), IC20.18 (1B1), J7.26, RN1.5 (R4)
BE: IC1.33 (2A2), IC3.14 (2A0), IC4.2 (A), IC11.3 (2A), J7.20, RN4.5 (R4)
Bank Latch: IC4.1 (B), IC5.11 (LE), J7.30
D0: IC1.47 (1A0), J7.53
D1: IC1.46 (1A1), J7.52
D2: IC1.44 (1A2), J7.51
D3: IC1.43 (1A3), J7.50
D4: IC1.41 (1A4), J7.49
D5: IC1.40 (1A5), J7.48
D6: IC1.38 (1A6), J7.47
D7: IC1.37 (1A7), J7.46
DE: IC3.13 (2A1), J7.45, R2.2
E: IC2.39 (E), IC9.10 (~2SD), J7.54
GND: C1.2, C2.2, C3.2, C4.2, C5.2, C6.2, C7.2, C8.2, C9.2, C10.2, C11.2, C12.2, C13.2, C14.2, C15.2, C16.2, C17.2, C18.2, C19.2, C20.2, C21.2, C23.2, C41.2, C42.2, IC1.4 (GND), IC1.10 (GND), IC1.13 (2B0), IC1.14 (2B1), IC1.15 (GND), IC1.21 (GND), IC1.25 (2~OE), IC1.28 (GND), IC1.34 (GND), IC1.35 (2A1), IC1.36 (2A0), IC1.39 (GND), IC1.45 (GND), IC2.1 (GND), IC2.23 (GND), IC2.24 (GND), IC3.8 (GND), IC4.3 (GND), IC5.10 (GND), IC6.7 (GND), IC7.4 (GND), IC8.3 (GND), IC9.7 (GND), IC9.11 (2CP), IC9.12 (2D), IC10.2 (GND), IC11.2 (GND), IC12.2 (GND), IC13.2 (GND), IC13.6 (C), IC14.2 (GND), IC16.3 (GND), IC18.1 (1A), IC18.2 (1B), IC18.4 (GND), IC19.4 (GND), IC20.10 (GND), IC36.2 (GND), J7.10, J7.23, J7.42, J7.55
M: IC6.9 (2Q), J7.64
Native Latch: IC9.9 (2Q), J7.57
unnamed: IC1.23 (2B7), R3.1
Opcode Valid: IC7.7 (1Y), J7.1
PHI2: IC1.26 (2A7), IC11.1 (1A), J7.39
RDY: IC2.3 (RDY), J7.21, R1.2
R~W: IC1.1 (1DIR), IC2.38 (R~W), IC3.2 (1A0), J7.24, R4.2
VDA: IC2.43 (VDA), IC7.5 (2A), IC8.2 (A), IC16.1 (B), J7.59
VPA: IC2.8 (VPA), IC7.6 (2B), IC8.1 (B), IC16.2 (A), J7.56
VPA·VDA: IC7.2 (1B), IC7.3 (2Y), J7.62
X: IC6.5 (1Q), J7.63
~ABORT: IC1.32 (2A3), J7.44, RN4.6 (R3)
~BANK 0: IC14.4 (Y), J7.33
~Data Output: IC3.15 (~2E), J7.58
~IRQ: IC1.30 (2A4), J7.43, RN4.7 (R2)
~ML: IC2.6 (~ML), J7.32
~NMI: IC1.29 (2A5), J7.41, RN4.8 (R1)
~PHI2: IC6.11 (2CP), IC9.3 (1CP), IC11.6 (1Y), J7.25
~RD: IC19.3 (2Y), J7.61
~Reset: IC1.27 (2A6), IC6.4 (~1SD), IC6.10 (~2SD), IC9.13 (~2RD), J7.40
~VP: IC2.2 (~VP), J7.31
~WD: IC19.6 (1Y), J7.60
